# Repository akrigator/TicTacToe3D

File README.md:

TicTacToe3D
===========

Проект реализует игру в трехмерные крестики-нолики при помощи Arduino UNO.

После запуска игроки делают ходы друг за другом, пока игровое поле не будет заполнено или места не будет достаточно для кона. По завершению игры строится списки построенных линий каждым игроком. С задержкой 1-2 секунды отображаются по одной линии каждого игрока. Таким образом наглядно демонстрируются все линии и возможное превосходство победителя: если начали отображатся линии одного цвета, то игрок этого цвета победил.

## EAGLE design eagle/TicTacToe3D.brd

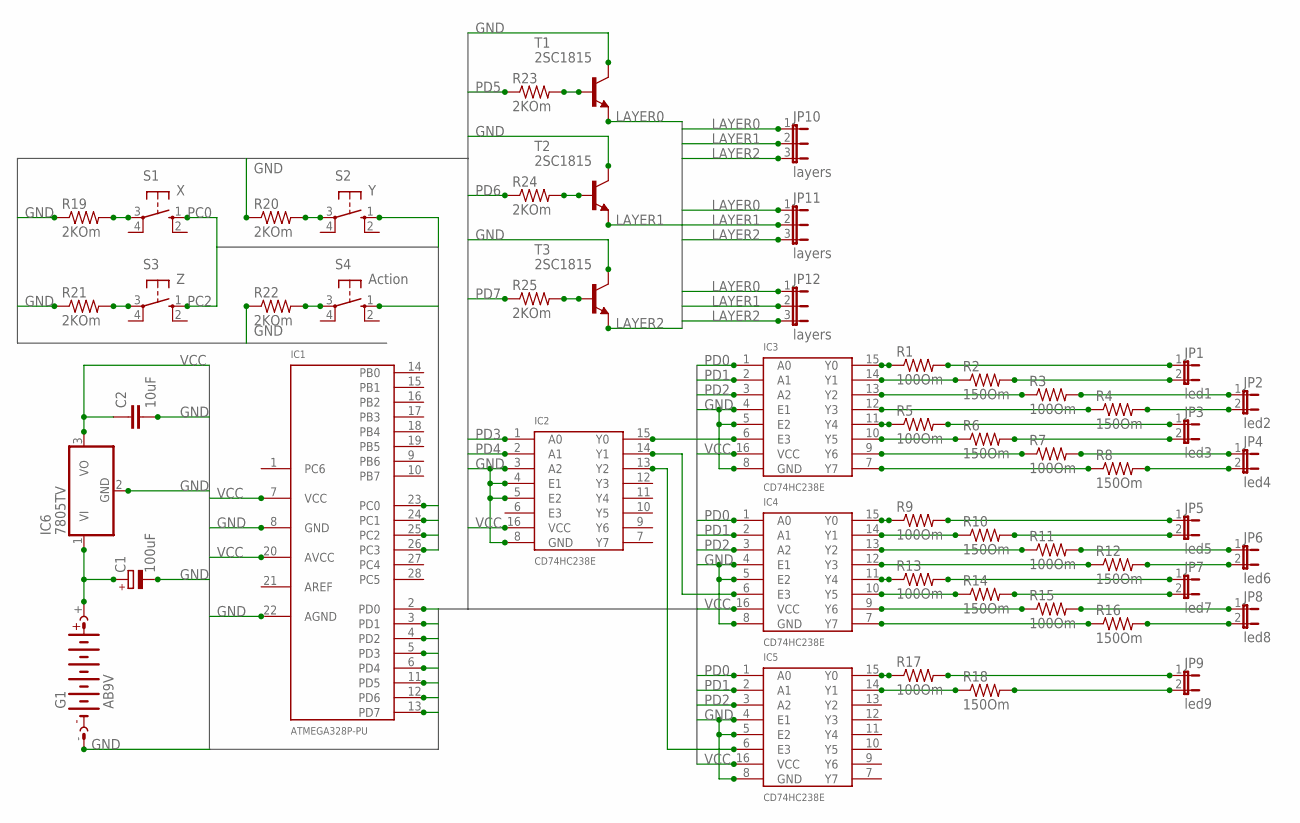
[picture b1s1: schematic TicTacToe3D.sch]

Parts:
C1: 100uF; E2-4
C2: 10uF; C050-024X044
G1: AB9V
IC1: ATMEGA328P-PU; 28P3
IC2, IC3, IC4, IC5: CD74HC238E; 16PDIP
IC6: 7805TV; TO220V
JP1: led1; JP1
JP2: led2; JP1
JP3: led3; JP1
JP4: led4; JP1
JP5: led5; JP1
JP6: led6; JP1
JP7: led7; JP1
JP8: led8; JP1
JP9: led9; JP1
JP10, JP11, JP12: layers; JP2
R1, R3, R5, R7, R9, R11, R13, R15, R17: 100Om; 0204/7
R2, R4, R6, R8, R10, R12, R14, R16, R18: 150Om; 0204/7
R19, R20, R21, R22, R23, R24, R25: 2KOm; 0204/7
S1: X; B3F-10XX
S2: Y; B3F-10XX
S3: Z; B3F-10XX
S4: Action; B3F-10XX
T1, T2, T3: 2SC1815; TO92-ECB

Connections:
GND: C1.-, C2.2, G1.-, IC1.8 (GND), IC1.22 (AGND), IC2.3 (A2), IC2.4 (E1), IC2.5 (E2), IC2.8 (GND), IC3.4 (E1), IC3.5 (E2), IC3.8 (GND), IC4.4 (E1), IC4.5 (E2), IC4.8 (GND), IC5.4 (E1), IC5.5 (E2), IC5.8 (GND), IC6.2 (GND), R19.1, R20.1, R21.1, R22.1, T1.C, T2.C, T3.C
LAYER0: JP10.1, JP11.1, JP12.1, T1.E
LAYER1: JP10.2, JP11.2, JP12.2, T2.E
LAYER2: JP10.3, JP11.3, JP12.3, T3.E
unnamed: C1.+, G1.+, IC6.1 (VI)
unnamed: IC2.15 (Y0), IC3.6 (E3)
unnamed: IC2.14 (Y1), IC4.6 (E3)
unnamed: IC2.13 (Y2), IC5.6 (E3)
unnamed: IC3.15 (Y0), R1.1
unnamed: IC3.14 (Y1), R2.1
unnamed: IC3.12 (Y3), R4.1
unnamed: IC3.13 (Y2), R3.1
unnamed: IC5.14 (Y1), R18.1
unnamed: R19.2, S1.3
unnamed: R20.2, S2.3
unnamed: R21.2, S3.3
unnamed: IC3.11 (Y4), R5.1
unnamed: IC3.10 (Y5), R6.1
unnamed: IC3.9 (Y6), R7.1
unnamed: IC3.7 (Y7), R8.1
unnamed: R22.2, S4.3
unnamed: R24.2, T2.B
unnamed: R25.2, T3.B
unnamed: R23.2, T1.B
unnamed: JP1.2, R2.2
unnamed: JP2.2, R4.2
unnamed: JP3.2, R6.2
unnamed: JP4.2, R8.2
unnamed: JP5.2, R10.2
unnamed: JP6.2, R12.2
unnamed: JP7.2, R14.2
unnamed: JP8.2, R16.2
unnamed: IC4.15 (Y0), R9.1
unnamed: IC4.14 (Y1), R10.1
unnamed: IC4.13 (Y2), R11.1
unnamed: IC4.12 (Y3), R12.1
unnamed: IC4.11 (Y4), R13.1
unnamed: IC4.10 (Y5), R14.1
unnamed: IC4.9 (Y6), R15.1
unnamed: IC4.7 (Y7), R16.1
unnamed: IC5.15 (Y0), R17.1
unnamed: JP9.2, R18.2
unnamed: JP1.1, R1.2
unnamed: JP2.1, R3.2
unnamed: JP3.1, R5.2
unnamed: JP4.1, R7.2
unnamed: JP5.1, R9.2
unnamed: JP6.1, R11.2
unnamed: JP7.1, R13.2
unnamed: JP8.1, R15.2
unnamed: JP9.1, R17.2
PC0: IC1.23 (PC0), S1.1 (S)
PC1: IC1.24 (PC1), S2.1 (S)
PC2: IC1.25 (PC2), S3.1 (S)
PC3: IC1.26 (PC3), S4.1 (S)
PD0: IC1.2 (PD0), IC3.1 (A0), IC4.1 (A0), IC5.1 (A0)
PD1: IC1.3 (PD1), IC3.2 (A1), IC4.2 (A1), IC5.2 (A1)
PD2: IC1.4 (PD2), IC3.3 (A2), IC4.3 (A2), IC5.3 (A2)
PD3: IC1.5 (PD3), IC2.1 (A0)
PD4: IC1.6 (PD4), IC2.2 (A1)
PD5: IC1.11 (PD5), R23.1
PD6: IC1.12 (PD6), R24.1
PD7: IC1.13 (PD7), R25.1
VCC: C2.1, IC1.7 (VCC), IC1.20 (AVCC), IC2.16 (VCC), IC3.16 (VCC), IC4.16 (VCC), IC5.16 (VCC), IC6.3 (VO)

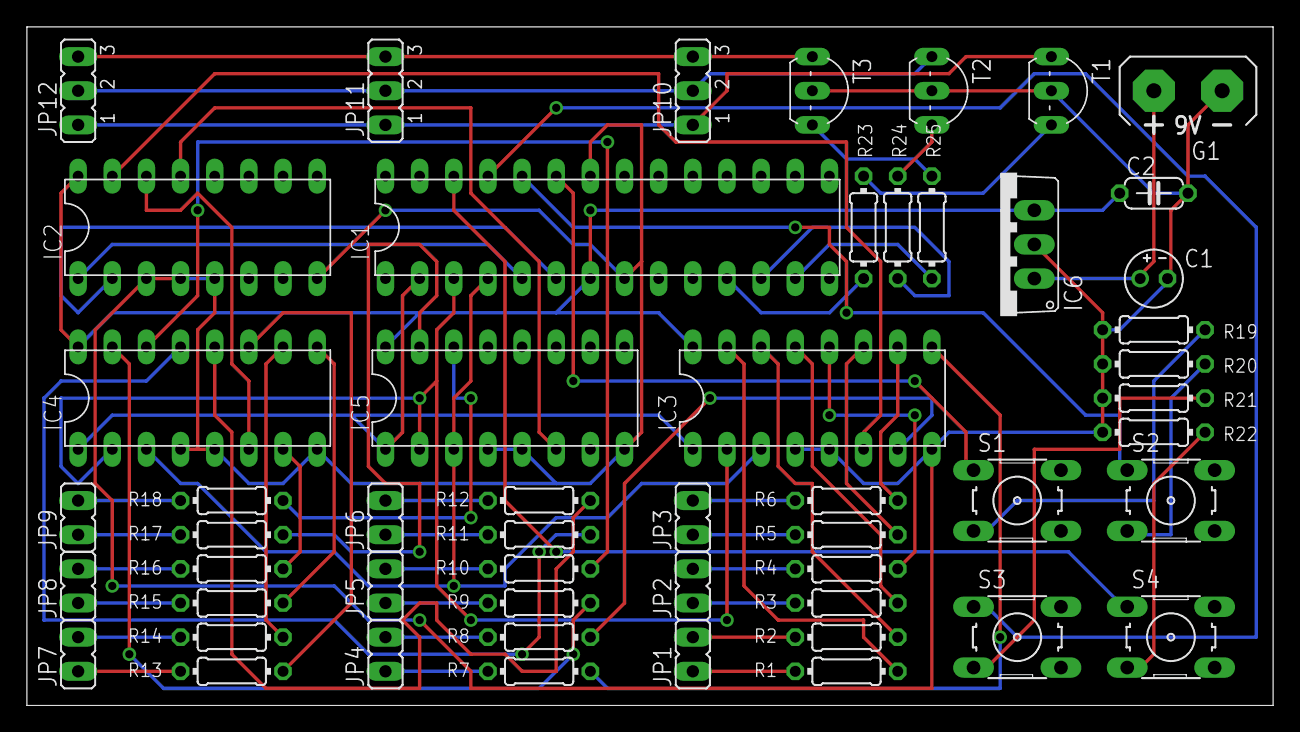
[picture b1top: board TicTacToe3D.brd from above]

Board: 2 copper layers, 92.7 x 50.5 mm, 53 parts (0 on the bottom side), 64 nets.

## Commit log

2013-12-08 That is developed already
2013-12-13 The search of straights is implemented
    Each player has an own list of straights. The lists are made after game
    field filled.
    The useless code is removed.
    The ignore file is modified for Atmel Studio project.
2013-12-15 Show players' straights at the game over
    The straight of the each player is displayed at the one moment. The
    game is restarted after all straights are shown.
2013-12-15 Fix a search of straights
2013-12-17 Supply of the decoder power pin is removed
    LEDs turn off via cathode's supply interruption instead of anode.
2014-01-21 Replace buttons + fixing issue of the rules
    The rule with 7 straight step is fixed.
2014-01-27 Add eagle project
